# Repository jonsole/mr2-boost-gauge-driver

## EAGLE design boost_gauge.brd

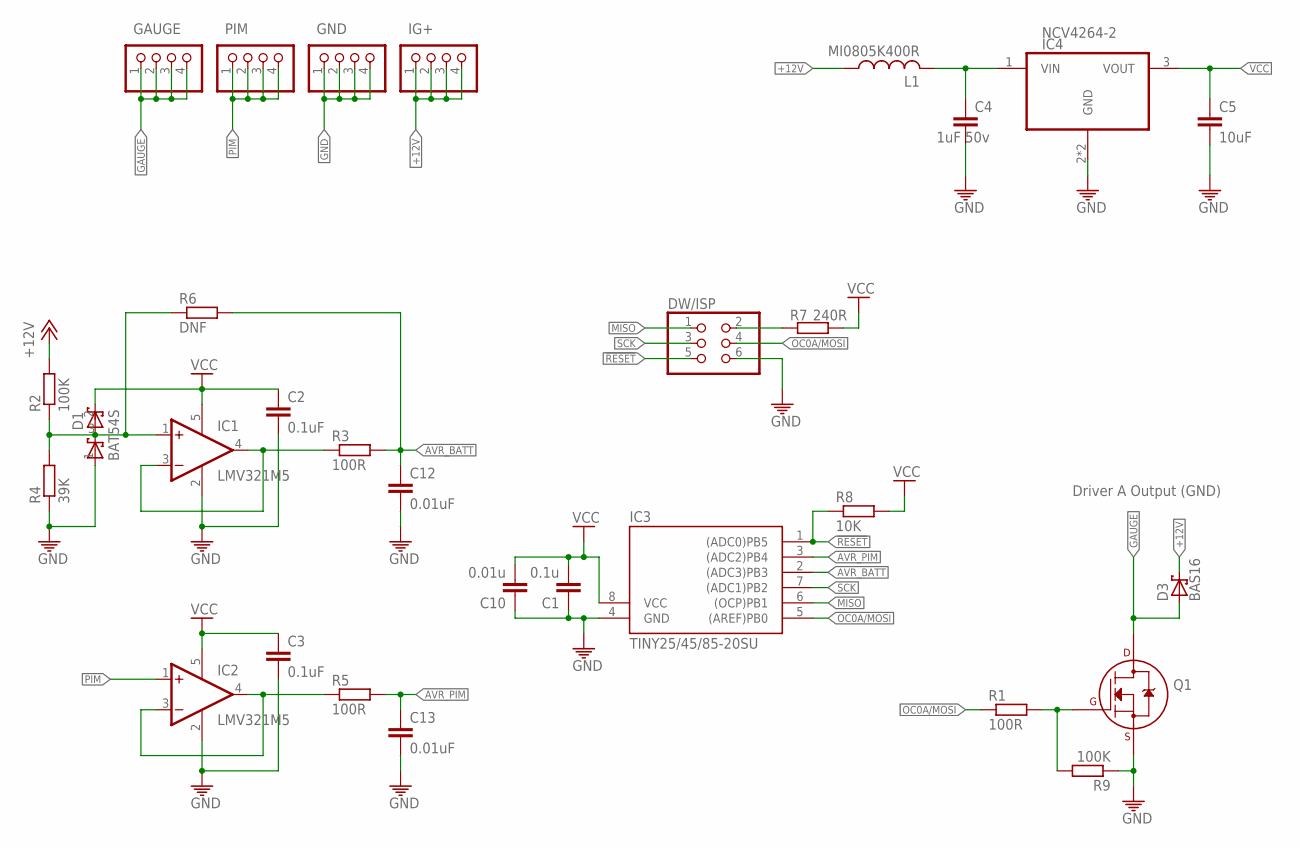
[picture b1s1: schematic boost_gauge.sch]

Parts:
C1: 0.1u; C0603
C2, C3: 0.1uF; C0603
C4: 1uF 50v; C0603
C5: 10uF; C1206
C10: 0.01u; C0603
C12, C13: 0.01uF; C0603
D1: BAT54S; SOT23
D3: BAS16; SOT23
DW/ISP: PINHD-2X3; 2X03
GAUGE: PCB-2
GND: PCB-2
IC1, IC2: LMV321M5; SOT23-5
IC3: TINY25/45/85-20SU; SOIC8
IC4: NCV4264-2; SOT223
IG+: PCB-2
L1: MI0805K400R; R0805
PIM: PCB-2
Q1: 2N7002A; SOT23
R1, R3, R5: 100R; R0603
R2, R9: 100K; R0603
R4: 39K; R0603
R6: DNF; R0603
R7: 240R; R0603
R8: 10K; R0603

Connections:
!RESET: DW/ISP.5, IC3.1 ((ADC0)PB5), R8.1
+12V: D3.3 (C), IG+.1, IG+.2, IG+.3, IG+.4, L1.1, R2.2
AVR_BATT: C12.1, IC3.2 ((ADC3)PB3), R3.2, R6.2
AVR_PIM: C13.1, IC3.3 ((ADC2)PB4), R5.2
GAUGE: D3.1 (A), GAUGE.1, GAUGE.2, GAUGE.3, GAUGE.4, Q1.3 (D)
GND: C1.1, C2.2, C3.2, C4.2, C5.2, C10.1, C12.2, C13.2, D1.1 (A1), DW/ISP.6, GND.1, GND.2, GND.3, GND.4, IC1.2 (V-), IC2.2 (V-), IC3.4 (GND), IC4.2 (GND), IC4.4 (GND), Q1.2 (S), R4.1, R9.1
MISO: DW/ISP.1, IC3.6 ((OCP)PB1)
unnamed: IC1.3 (-IN), IC1.4 (OUT), R3.1
unnamed: D1.3 (C1A2), IC1.1 (+IN), R2.1, R4.2, R6.1
unnamed: IC2.3 (-IN), IC2.4 (OUT), R5.1
unnamed: C4.1, IC4.1 (VIN), L1.2
unnamed: Q1.1 (G), R1.2, R9.2
unnamed: DW/ISP.2, R7.1
OC0A/MOSI: DW/ISP.4, IC3.5 ((AREF)PB0), R1.1
PIM: IC2.1 (+IN), PIM.1, PIM.2, PIM.3, PIM.4
SCK: DW/ISP.3, IC3.7 ((ADC1)PB2)
VCC: C1.2, C2.1, C3.1, C5.1, C10.2, D1.2 (C2), IC1.5 (V+), IC2.5 (V+), IC3.8 (VCC), IC4.3 (VOUT), R7.2, R8.2

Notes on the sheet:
Driver A Output (GND)

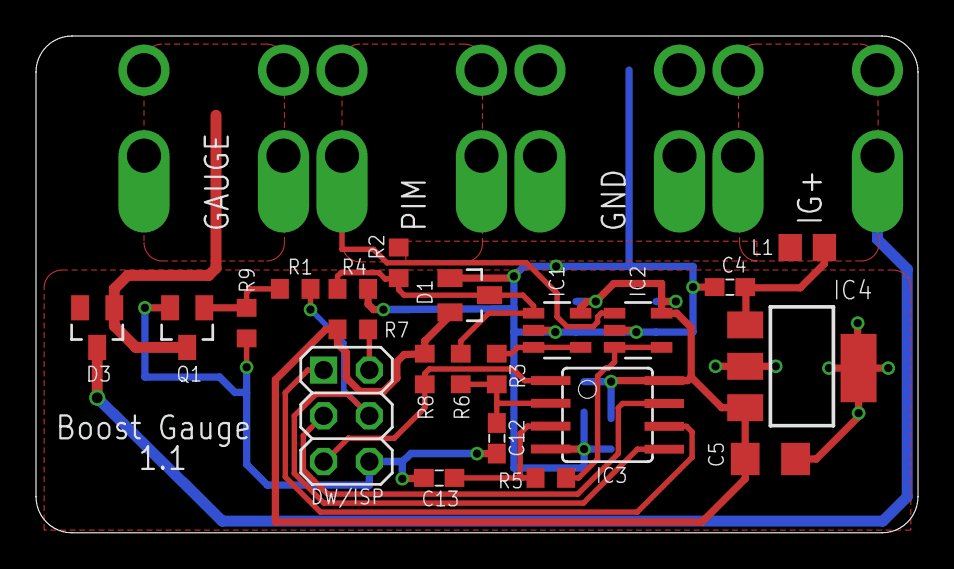
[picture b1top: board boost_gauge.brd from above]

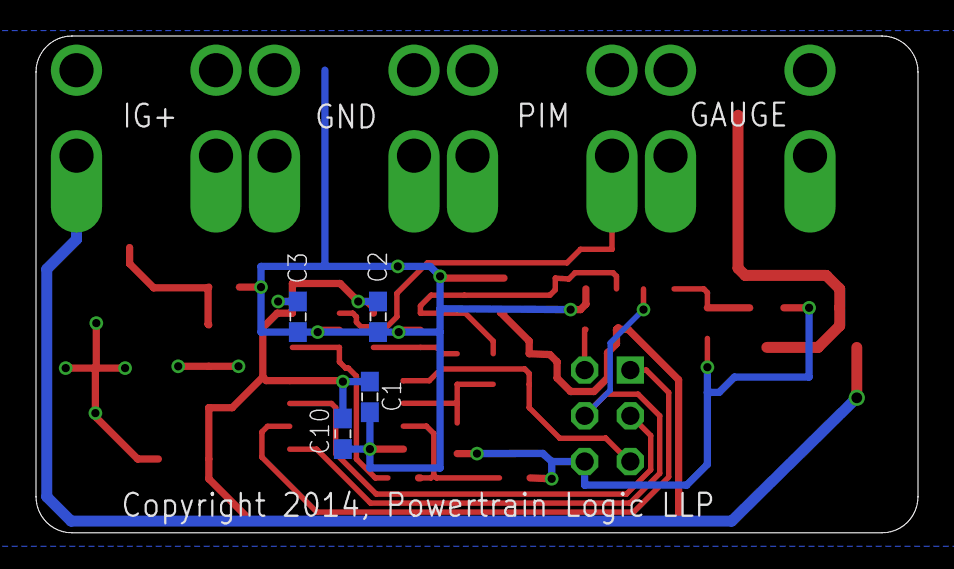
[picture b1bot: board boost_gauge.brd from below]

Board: 2 copper layers, 49.0 x 27.6 mm, 30 parts (4 on the bottom side), 17 nets.

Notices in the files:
boost_gauge.brd:
Copyright 2014, Powertrain Logic LLP
